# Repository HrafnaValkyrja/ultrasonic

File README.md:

# Stereo Ultrasound

A glasses-mounted wearable that shifts ultrasound (≈20–85 kHz) down into the audible range and plays it by bone conduction, in stereo, in real time.

- **Spec (source of truth):** [`docs/spec.md`](docs/spec.md). §1 is the owner-locked MVP.
- **Latest plan review:** [`docs/research/review-2026-09-30.md`](docs/research/review-2026-09-30.md)
- **Research findings:** [`docs/research/`](docs/research/), one file per task ID from spec §12.
- **Models and checks:** [`sim/checks/`](sim/checks/): PWM noise, noise-shaper comparison, dead-time distortion, weight balance. Run with `python3 <script>` (numpy, scipy).
- **Data:** [`sim/data/`](sim/data/): the mic's ultrasonic response, digitized from its datasheet.

Status: concept phase. Phase 1 (DSP simulation in Python) is next, pending owner decisions O1–O3 in spec §12.

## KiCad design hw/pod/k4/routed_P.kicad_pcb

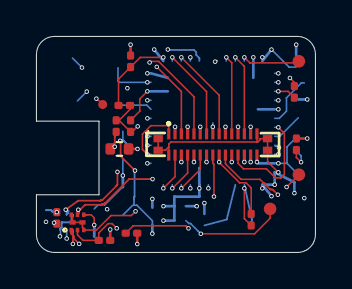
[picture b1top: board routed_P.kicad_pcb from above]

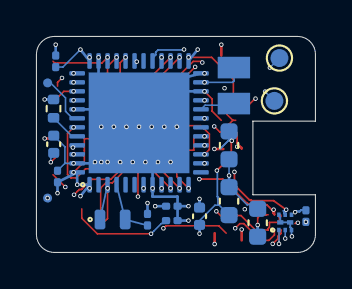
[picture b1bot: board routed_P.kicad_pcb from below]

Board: 6 copper layers, 15.5 x 12.0 mm, 37 parts (20 on the bottom side), 35 nets.

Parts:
C1, C2, C3, C6, C10: 100n; C_0201_0603Metric
C4, C7: 10u; C_0603_1608Metric
C5: 1u; C_0402_1005Metric
C8: 2u2 10V; C_0402_1005Metric
C9: 2u2 10V; C_0201_0603Metric
C11, C12: 8p2; C_0201_0603Metric
C14: 22u; C_0603_1608Metric
C22: 10n; C_0201_0603Metric
J1: XDCR_A; TestPoint_Pad_D1.0mm
J2: XDCR_B; TestPoint_Pad_D1.0mm
J21: BM28B0.6-30DP/2-0.35V(51); BM28B0.6-30DP_2-0.35V
L1: 2u2; L0806
Q1, Q2: PMCXB290UE; Nexperia_SOT1216_DFN1010B-6
R1: 10k; R_0402_1005Metric
R2: 33; R_0201_0603Metric
R3, R4, R5, R6: 100k; R_0201_0603Metric
R21: 0.1; R_0402_1005Metric
R22: 1k; R_0201_0603Metric
R23: 1M; R_0201_0603Metric
TP1: SWDIO; TestPoint_Pad_D0.7mm
TP2: SWCLK; TestPoint_Pad_D0.7mm
TP3: NRST; TestPoint_Pad_D0.7mm
TP7: DBG_TX; TestDot_D0.5mm
TP8: MDF_CCK; TestDot_D0.5mm
TP9: MDF_SDI; TestDot_D0.5mm
U1: STM32U575CIUxQ; QFN-48-1EP_7x7mm_P0.5mm_EP5.6x5.6mm
Y1: 32.768k 7pF; Crystal_SMD_2012-2Pin_2.0x1.2mm

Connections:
+3V0: C1.1, C2.1, C3.1, C4.1, C5.1, C6.1, C7.1, C14.1, J21.15, J21.30, J21.31, J21.32, J21.33, J21.34, Q1.4, Q2.4, R3.2, R5.2, R23.1, U1.1, U1.9, U1.21, U1.25, U1.36, U1.48
BRIDGE_RTN: Q1.1, Q2.1, R21.1, R22.1
BTN: J21.25, U1.10
CHG_INT: J21.23, U1.38
DBG_TX: TP7.1, U1.42
GA_N: Q1.2, R4.1, U1.17
GA_P: Q1.5, R3.1, U1.29
GB_N: Q2.2, R6.1, U1.28
GB_P: Q2.5, R5.1, U1.31
GND: C1.2, C2.2, C3.2, C4.2, C5.2, C6.2, C7.2, C8.2, C9.2, C10.2, C11.2, C12.2, C14.2, C22.2, J21.2, J21.4, J21.6, J21.8, J21.10, J21.12, J21.14, J21.16, J21.17, J21.18, J21.20, J21.22, J21.24, J21.26, J21.28, R1.2, R4.2, R6.2, R21.2, U1.8, U1.22, U1.24, U1.35, U1.41, U1.47, U1.49
I2C_SCL: J21.7, U1.26
I2C_SDA: J21.9, U1.27
I_SENSE: C22.1, R22.2, R23.2, U1.16
LED_K: J21.19, U1.43
LSE_IN: C11.1, U1.3, Y1.1
LSE_OUT: C12.1, U1.4, Y1.2
MDF_CCK: TP8.1, U1.45
MDF_SDI: TP9.1, U1.19
MIC_CLK: J21.3, R2.2
MIC_DATA: J21.21, U1.40
MIC_VDD: J21.1, U1.15
unnamed: R1.1, U1.44
unnamed: R2.1, U1.39
NRST: C10.1, TP3.1, U1.7
OUT_A: J1.1, Q1.3, Q1.6, Q1.7, Q1.8
OUT_B: J2.1, Q2.3, Q2.6, Q2.7, Q2.8
SWCLK: TP2.1, U1.37
SWDIO: TP1.1, U1.34
TS: J21.29, U1.12
USB_DM: J21.11, U1.32
USB_DP: J21.13, U1.33
VBAT_SENSE: J21.5, U1.14
VBUS_SENSE: J21.27, U1.11
VDD11: C8.1, C9.1, L1.2, U1.23, U1.46
VLXSMPS: L1.1, U1.20

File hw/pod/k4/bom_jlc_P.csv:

Comment,Designator,Footprint,LCSC Part #,Qty,In sourcing lock
100n,"C1,C10,C2,C3,C6",C_0201_0603Metric,C76934,5,yes
8p2,"C11,C12",C_0201_0603Metric,C161441,2,yes
22u,C14,C_0603_1608Metric,C59461,1,yes
10n,C22,C_0201_0603Metric,C85930,1,yes
10u,"C4,C7",C_0603_1608Metric,C19702,2,yes
1u,C5,C_0402_1005Metric,C52923,1,yes
2u2 10V,C8,C_0402_1005Metric,C107369,1,yes
2u2 10V,C9,C_0201_0603Metric,C318539,1,yes
BM28B0.6-30DP/2-0.35V(51),J21,BM28B0.6-30DP_2-0.35V,C424570,1,yes
2u2,L1,L0806,C337891,1,yes
PMCXB290UE,"Q1,Q2",Nexperia_SOT1216_DFN1010B-6,C19654206,2,yes
10k,R1,R_0402_1005Metric,C25744,1,yes
33,R2,R_0201_0603Metric,C473457,1,yes
0.1,R21,R_0402_1005Metric,C409058,1,yes
1k,R22,R_0201_0603Metric,C270365,1,yes
1M,R23,R_0201_0603Metric,C473482,1,yes
100k,"R3,R4,R5,R6",R_0201_0603Metric,C270364,4,yes
STM32U575CIUxQ,U1,QFN-48-1EP_7x7mm_P0.5mm_EP5.6x5.6mm,C5271013,1,yes
32.768k 7pF,Y1,Crystal_SMD_2012-2Pin_2.0x1.2mm,C99009,1,yes

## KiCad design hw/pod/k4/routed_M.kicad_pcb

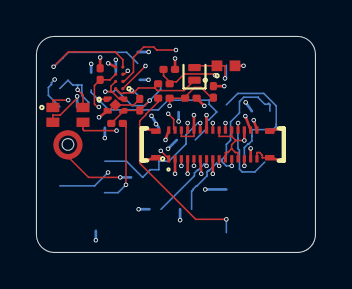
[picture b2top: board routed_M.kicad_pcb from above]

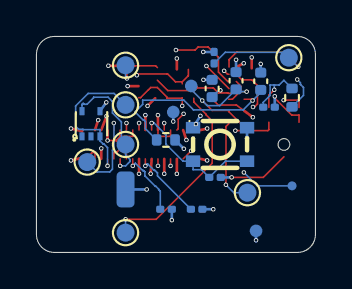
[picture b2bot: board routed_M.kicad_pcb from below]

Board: 6 copper layers, 15.5 x 12.0 mm, 38 parts (24 on the bottom side), 22 nets.

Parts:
C13, C19: 100n; C_0201_0603Metric
C15: 4u7 25V; C_0402_1005Metric
C16: 2u2 10V; C_0201_0603Metric
C17: 1u 16V; C_0201_0603Metric
C18: 1u; C_0402_1005Metric
C21: 10u; C_0402_1005Metric
D4: PMEG3005EL; D_SOD-882
D5: TPD1E10B06DPYR; X1SON-2_L1.0-W0.6-P0.65-BI-1
J3: VBUS; TestPoint_Pad_D1.0mm
J4: GND; WirePad_1.0x2.0mm
J5: BAT+; TestPoint_Pad_D1.0mm
J7: LED+; TestPoint_Pad_D1.0mm
J8: LED-; TestPoint_Pad_D1.0mm
J9: NTC; TestPoint_Pad_D1.0mm
J10: D+; TestPoint_Pad_D1.0mm
J11: D-; TestPoint_Pad_D1.0mm
J20: BM28B0.6-30DS/2-0.35V(51); BM28B0.6-30DS_2-0.35V
R8, R9: 1M; R_0201_0603Metric
R10, R14: 2k2; R_0201_0603Metric
R12, R13: 100k; R_0201_0603Metric
R15, R16: 10k; R_0201_0603Metric
R20: 0; R_0402_1005Metric
R30: 33; R_0402_1005Metric
RT1: 10k B3435; R_0201_0603Metric
SW1: KMT022NGJLHS; SW-SMD_4P-L3.0-W2.6-P1.85-LS3.4
TP4: 3V0; TestPoint_Pad_D0.7mm
TP5: GND; TestPoint_Pad_D0.7mm
TP6: VSYS; TestPoint_Pad_D0.7mm
TP10: MIC_DATA; TestDot_D0.5mm
U2: SPH0641LU4H-1; Knowles_LGA-5_3.5x2.65mm_Port0.65
U3: BQ25180YBGR; DSBGA-8_L1.6-W0.9-R2-C4-P0.40-BL
U4: TPS7A2030PDQNR; X2SON-4_L1.0-W1.0-P0.65-TL-EP
U6: TPD2E2U06DRLR; SOT-553-5_L1.6-W1.2-P0.50-LS1.6-TL-1

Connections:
+3V0: J20.15, J20.30, J20.31, J20.32, J20.33, J20.34, R15.2, R16.2, R20.2, SW1.1, SW1.2, TP4.1
BTN: J20.25, R10.1, SW1.3, SW1.4
CHG_INT: J20.23, U3.A1
DOCK_VBUS: D4.2, D5.1, J3.1
GND: C13.2, C15.2, C16.2, C17.2, C18.2, C19.2, C21.2, D5.2, J4.1, J20.2, J20.4, J20.6, J20.8, J20.10, J20.12, J20.14, J20.16, J20.17, J20.18, J20.20, J20.22, J20.24, J20.26, J20.28, R9.2, R10.2, R13.2, RT1.2, TP5.1, U2.2, U2.3, U3.D2, U4.2, U4.5, U6.4
I2C_SCL: J20.7, R15.1, U3.B1
I2C_SDA: J20.9, R16.1, U3.C1
LDO_OUT: C18.1, R20.1, U4.1
LED_A: J7.1, R14.2
LED_K: J8.1, J20.19
MIC_CLK: J20.3, U2.4
MIC_DATA: J20.21, TP10.1, U2.1
MIC_VDD: J20.1, R30.1
MIC_VDDF: C13.1, R30.2, U2.5
TS: J9.1, J20.29, RT1.1, U3.D1
USB_DM: J11.1, J20.11, U6.5
USB_DP: J10.1, J20.13, U6.3
VBAT: C16.1, J5.1, R8.1, U3.C2
VBAT_SENSE: C19.1, J20.5, R8.2, R9.1
VBUS: C15.1, D4.1, R12.1, U3.A2
VBUS_SENSE: J20.27, R12.2, R13.1
VSYS: C17.1, C21.1, R14.1, TP6.1, U3.B2, U4.3, U4.4

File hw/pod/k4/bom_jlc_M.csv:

Comment,Designator,Footprint,LCSC Part #,Qty,In sourcing lock
100n,"C13,C19",C_0201_0603Metric,C76934,2,yes
4u7 25V,C15,C_0402_1005Metric,C2858031,1,yes
2u2 10V,C16,C_0201_0603Metric,C318539,1,yes
1u 16V,C17,C_0201_0603Metric,C318540,1,yes
1u,C18,C_0402_1005Metric,C52923,1,yes
10u,C21,C_0402_1005Metric,C315248,1,yes
PMEG3005EL,D4,D_SOD-882,C282565,1,yes
TPD1E10B06DPYR,D5,X1SON-2_L1.0-W0.6-P0.65-BI-1,C48260,1,yes
BM28B0.6-30DS/2-0.35V(51),J20,BM28B0.6-30DP_2-0.35V,C424571,1,yes
2k2,"R10,R14",R_0201_0603Metric,C473508,2,yes
100k,"R12,R13",R_0201_0603Metric,C270364,2,yes
10k,"R15,R16",R_0201_0603Metric,C473048,2,yes
0,R20,R_0402_1005Metric,C17168,1,yes
33,R30,R_0402_1005Metric,C25105,1,yes
1M,"R8,R9",R_0201_0603Metric,C473482,2,yes
10k B3435,RT1,R_0201_0603Metric,C98098,1,yes
KMT022NGJLHS,SW1,SW-SMD_4P-L3.0-W2.6-P1.85-LS3.4,C221707,1,yes
SPH0641LU4H-1,U2,Knowles_LGA-5_3.5x2.65mm_Port0.65,C2879853,1,yes
BQ25180YBGR,U3,DSBGA-8_L1.6-W0.9-R2-C4-P0.40-BL,C3682423,1,yes
TPS7A2030PDQNR,U4,X2SON-4_L1.0-W1.0-P0.65-TL-EP,C5220164,1,yes
TPD2E2U06DRLR,U6,SOT-553-5_L1.6-W1.2-P0.50-LS1.6-TL-1,C1972959,1,yes

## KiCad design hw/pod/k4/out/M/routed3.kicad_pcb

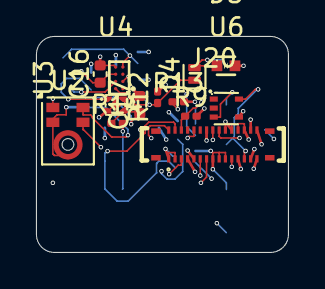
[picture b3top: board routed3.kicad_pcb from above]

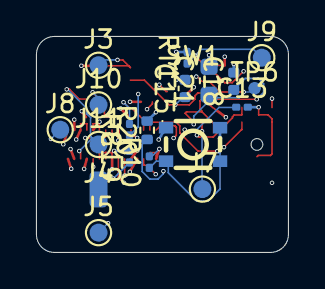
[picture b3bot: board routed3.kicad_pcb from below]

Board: 6 copper layers, 14.0 x 12.0 mm, 32 parts (19 on the bottom side), 21 nets.

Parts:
C13, C19: C_0201_0603Metric
C15, C16, C17, C18: C_0402_1005Metric
C21: C_0603_1608Metric
D4: D_SOD-882
D5: X1SON-2_L1.0-W0.6-P0.65-BI-1
J3, J5, J7, J8, J9, J10, J11: TestPoint_Pad_D1.0mm
J4: WirePad_1.0x2.0mm
J20: CONN-SMD_BM28B0.6-30DS-2-0.35V-51; BM28B0.6-30DS_2-0.35V
R8, R9, R10, R12, R13, R14: R_0201_0603Metric
R20: R_0402_1005Metric
RT1: R_0201_0603Metric
SW1: SW-SMD_4P-L3.0-W2.6-P1.85-LS3.4
TP6: TestPoint_Pad_D0.7mm
U2: Knowles_LGA-5_3.5x2.65mm; Knowles_LGA-5_3.5x2.65mm_Port0.65
U3: DSBGA-8_L1.6-W0.9-R2-C4-P0.40-BL
U4: X2SON-4_L1.0-W1.0-P0.65-TL-EP
U6: SOT-553-5_L1.6-W1.2-P0.50-LS1.6-TL-1

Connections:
+3V0: J20.17, J20.18, J20.19, R20.2, SW1.1, SW1.2
BTN: J20.29, R10.1, SW1.3, SW1.4
CHG_INT: J20.27, U3.A1
DOCK_VBUS: D4.2, D5.1, J3.1
GND: C13.2, C15.2, C16.2, C17.2, C18.2, C19.2, C21.2, D5.2, J4.1, J20.1, J20.2, J20.4, J20.5, J20.8, J20.9, J20.10, J20.12, J20.14, J20.15, J20.16, J20.20, J20.21, J20.24, R9.2, R10.2, R13.2, RT1.2, U2.2, U2.3, U3.D2, U4.2, U4.5, U6.4
I2C_SCL: J20.23, U3.B1
I2C_SDA: J20.25, U3.C1
LDO_OUT: C18.1, R20.1, U4.1
LED_A: J7.1, R14.2
LED_K: J8.1, J20.30
MIC_CLK: J20.3, U2.4
MIC_DATA: J20.7, U2.1
MIC_VDD: C13.1, J20.6, U2.5
TS: J9.1, J20.22, RT1.1, U3.D1
USB_DM: J11.1, J20.13, U6.5
USB_DP: J10.1, J20.11, U6.3
VBAT: C16.1, J5.1, R8.1, U3.C2
VBAT_SENSE: C19.1, J20.28, R8.2, R9.1
VBUS: C15.1, D4.1, R12.1, U3.A2
VBUS_SENSE: J20.26, R12.2, R13.1
VSYS: C17.1, C21.1, R14.1, TP6.1, U3.B2, U4.3, U4.4

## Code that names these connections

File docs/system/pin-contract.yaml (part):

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# Entry fields
#   id         function name (the net name where the net has one)
#   net        net name in the SKiDL schematic (hw/pod/gen.py), as in integration-map.md Section 3
#   via        for a net with no name of its own: {ref: R2, from_net: MIC_CLK} = the net on R2's OTHER terminal. The U1 pin is there
#   signal     required signal. An ST signal name (TIM1_CH1), or one of
#                GPIO        the pin is a plain GPIO; `modes` (Output, EXTI) must be in its IOModes
#                NRST        the reset pin (ST pin type Reset)
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  # ---- F1 hear: PDM clock out and data in on the ADF1 filter, supply switched by a GPIO
  - {id: MIC_CLK, via: {ref: R2, from_net: MIC_CLK}, signal: ADF1_CCK0, af: 3, role: "PDM clock to the mic through R2 33R (F1)"}
  - {id: MIC_DATA, net: MIC_DATA, signal: ADF1_SDI0, af: 3, role: "PDM data from the mic (F1)"}
  - {id: MIC_VDD, net: MIC_VDD, signal: GPIO, modes: [Output], role: "GPIO-switched mic supply, off in Off mode (F1, D12)"}
  # ---- F13 charger link
  - {id: I2C_SCL, net: I2C_SCL, signal: I2C2_SCL, af: 4, role: "charger I2C clock (F13)"}
  - {id: I2C_SDA, net: I2C_SDA, signal: I2C2_SDA, af: 4, role: "charger I2C data (F13)"}
  - {id: CHG_INT, net: CHG_INT, signal: GPIO, modes: [EXTI], role: "charger interrupt (F13): a GPIO with EXTI"}
  # ---- F10 USB data
  - {id: USB_DM, net: USB_DM, signal: USB_OTG_FS_DM, af: 10, role: "USB full-speed D- (F10)"}
  - {id: USB_DP, net: USB_DP, signal: USB_OTG_FS_DP, af: 10, role: "USB full-speed D+ (F10)"}
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  - {id: BOOT0, via: {ref: R1, from_net: GND}, signal: BOOT0, role: "BOOT0 held low by R1 10k (F14)"}
  # Rev F: BOOT_RX (R11 on PA10) and CC_SENSE (R19 on PA3) removed with their parts: the ROM loader pulls PA10 up itself
  # (AN2606 Rev 69 Table 199); charge-current policy comes from enumeration, not CC (simplification study PER-02, PWR-03)
  - {id: DBG_TX, net: DBG_TX, signal: USART1_TX, af: 7, role: "printf telemetry on TP7 (F14, O18; PER-12): SWO is lost to the mic clock on PB3"}
  - {id: MDF_CCK, net: MDF_CCK, signal: MDF1_CCK0, af: 5, role: "mic-clock fallback dot TP8 (F1, O18; sub-audio-in issue 5): hand-wire to R2's mic-side pad if the ADF clock duty fails"}
  - {id: MDF_SDI, net: MDF_SDI, signal: MDF1_SDI0, af: 6, role: "mic-data fallback dot TP9, wired to TP10 (MIC_DATA) in the fallback (F1, O18)"}
  # ---- F2 / F11 / F12
  - {id: LSE_IN, net: LSE_IN, signal: RCC_OSC32_IN, role: "32.768 kHz crystal (F2)"}
  - {id: LSE_OUT, net: LSE_OUT, signal: RCC_OSC32_OUT, role: "32.768 kHz crystal (F2)"}
  - {id: BTN, net: BTN, signal: PWR_WKUP1, role: "button wake from Off/Stop (F11)"}
  - {id: LED_K, net: LED_K, signal: TIM4_CH2, af: 2, role: "LED cathode, open-drain, duty set from VBAT (F12); gen.py: PB7 TIM4_CH2"}

# What the pins do besides their job. Sources are ST's datasheet and reference manual (text read 2026-10-02) and the audit
# docs/system/audit-datasheet-claims.md; ECR-0013 tracks every one.
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    cleared_by: {pin: PB5, net: GND}
  - port: PB15
    ecr: ECR-0013
    note: "UCPD dead battery: after reset a 5.1k pull-down (UCPD1_CC2) is activated by high level on PB14 (UCPD1_DBCC2 = I2C_SDA, idles high); a bridge N gate here is held OFF until PWR_UCPDR.UCPD_DBDIS is set"
    source: "ST DS13737 Rev 8 pin definitions table note 4; ECR-0013 S2"
    mitigation: firmware
  - port: PB4
    ecr: ECR-0013
    note: "after reset PB4 is NJTRST with an internal pull-up (30-50k to VDD): ~60 uA back-feeds the mic through MIC_DATA while its PA5-gated supply is off (reset, ROM DFU, Off); firmware must set PB4 analog / no pull before Off"
    source: "ST DS13737 Rev 8 pin definitions table note 5; RM0456 Rev 7 section 13.3.1 (audit claim 5)"
    mitigation: firmware
  - port: PA2
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  rule: "no switching node (VLXSMPS, VDD11, OUT_A/B) crosses the B2B; SMPS loop (U1, L1, C7, C8/C9) on one board (P)"
  on_M: "U2 mic + C13, U3 charger + C15/C16/C21, U4 LDO + C17/C18/R20, D4/D5/U6, dock pads J3/J4/J10/J11 (+2 magnets), SW1/R10, R8/R9/R12/R13/C19, RT1/J9, R14/J7/J8, J5, TP6, TP4/TP5/TP10, R15/R16 (I2C pull-ups), J20 (28 parts; rev 4 unload 2026-10-08)"
  on_P: "U1 + C1-C12, Y1, L1, R1/R2, Q1/Q2 + R3-R6, R21-R23/C22/C14, J1/J2, TP1-TP3/TP7-TP9, J21 (26 parts)"
  risks: ["BM28 numbering pin n <-> pin n and datasheet ratings [T]", "PA5/PB3/PB4 routing on P must stay away from L1/VLXSMPS (in-plane victim, V9 B_plus_noise.rerun_2026_10_08_partition_v2)"]

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
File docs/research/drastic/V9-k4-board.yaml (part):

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    noise: "same topology as today: port->L1 >= 12 mm, mic and MCU on one 17 mm board, 6L gives an extra inner-layer pair for mic return isolation. Unchanged risk class; tightest packing (MCU escape next to mic nets)."
  B_two_stacked_boards:
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    inter_board_signals: "~16-18 [E, pin-contract.yaml not read for the final map]: GND x4, VSYS x2 (bridge 315 mA peak, parallel pins), +3V0 x2, USB_DP, USB_DN, CHG_INT, I2C SDA/SCL (charger, PB6/PA1), BTN, plus 1-2 spares. 20-pin B2B suffices; 24 if SWD is routed through."
    L_mm: "~14.5 (range 14-15.5) [E]: floor from hard_floor (13.5) + 4 faces at ~U 0.35 + B2B footprint (~5.4 x 2 mm on each inner face) ; M is the length-setting board (QFN48 + L1 >= 12 mm behind the port); P can be shorter and ends earlier. Gain vs A(17): -2.5; vs A-WLCSP(15): only -0.5."
    pod_L_mm: "48.6"
    layers: "4L + 4L. Per-board ~100-118 pins on ~174 mm2 = 0.57-0.68 pins/mm2 = x1.05-1.25 of today's 0.543 (proven 4L ceiling x1.00, 'likely' <=1.15, 'possible' 1.15-1.5, V5 bands) -> 4L 'possible', 6L on M only is the fallback [M-L]"
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B_plus_noise:   # 2026-10-08 Claude (Opus 5.5 subagent). Sim: sim/noise/vertical_bplus.py (run_l2 reused unchanged, geometry hooks patched). Board: draft_r2 routed. H measured-by-model, all geometry/leak numbers [E] assumptions.
  rerun_2026_10_08_partition_v2:   # Claude (Opus 5.5 subagent), after the d2a70d9 review flaw (VLXSMPS/VDD11 crossed the B2B)
    partition: "ECR-0020 rev 2: P (upper) = U1 + SMPS (L1, C7, C8/C9) + charger + LDO + bridge + dock + button = ALL aggressors F01/F02; M (lower) = mic U2 + C13 only. B2B = BM28 10-pin: MIC_VDD, MIC_CLK, MIC_DATA + 7 GND. No switching node, no bridge or SMPS current crosses."
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  caveats:
    - "Margin to PSRR sign-off is thin in the pessimistic corner (4.8 dB < 10). Retire with a bring-up measurement (LN-V*) on a real stack; do not claim better than the model error (+-10 dB)."
    - "Conduction through BM28 not modelled (A6): the worst existing line (A01 conduction 15.3 dB) can only move down with extra series L/R in GND/VSYS. Needs >= 4 GND pins and a local 22 uF at the lower board (already in the B options)."
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    - "Mic is 1.08 mm, gap 0.6: the mic must be on the lower board's OUTER face; then the port opening is on the outer side and the planes shield the mic die from the upper board. If the mic sat inside the gap the shielding would drop out."
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  glossary: {PSRR: "power-supply rejection ratio of the mic", M_eff: "effective mutual inductance (nH) between aggressor and victim traces after plane screening", L1_body: "the 2.2 uH SMPS inductor modelled as one filament 0.5 mm off the board face"}
  noise:
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    why_not_extract_py: "extract.py/budget.py/pcbgeom.py assert 4 copper layers and ONE board; the MIC_VDD conduction network (U1 PA5 -> BM28 -> C13/mic) spans two boards and is not built. So conduction is NOT covered (K4-CONDUCT stays open)."
    result_margin_dB_F02_smps_on_mic_supply:   # tone chain, nominal / pessimistic PSRR / worst-case PSRR roll-off. sign-off needs >= 10 at worst
      today_draft_r2: [68.6, 48.6, 18.6]
      K4_traces_only_signed: [64.4, 44.4, 14.4]
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      - "owner decisions still open: ECR-0020/0021 approval, worst-PSRR noise corner, K4-BM28-DS contact R now read: signal <=100 mohm, power <=30 mohm max, K4-HEIGHTS, K4-STACK6."
    recommendation: "wait for K4-HEIGHTS + K4-STACK6 (both fast), then switch; making k4 default today would leave interfaces.py/bom_check/noise half-blind."
k4_mic_filter_2026_10_08:   # Claude (Opus 5.5 subagent). Follows k4_post_route_2026_10_08; ECR-0020 rev 5. P placement/routing not touched.
  glossary: {R30: "33 ohm series resistor on M between MIC_VDD (from P's PA5 via BM28 pin 6) and the mic-local net MIC_VDDF", MIC_VDDF: "filtered mic supply: U2 VDD + C13", K4-STACK6: "backlog item: record the JLC 6-layer 0.8 mm stack-up"}
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  model_corrections: "k4_noise.py c5899c1 did not mirror P (stack (x, 12 - y)) and put P file F.Cu on top; place_k4 says P file F is the INNER face. Fixed (--legacy-noflip reproduces the old geometry). Gap 0.6 (BM28 mated, [T]) instead of 1.3."
  result_F02_smps_to_mic_vdd_worst_PSRR_corner_dB:   # abs-bound margin with the L1 body, sign-off >= 10
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
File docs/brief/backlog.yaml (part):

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  - {id: ECR-0014/15/16, t: "simplification packages A/B/C still 'proposed'; superseded in practice by ECR-0018 (O25/O26)", opts: "close as superseded (rec) / keep open for the cherry-picks not in MZ-2", blk: owner}
  - {id: ECR-0018, t: "Phase-2 MZ-2 approved, implementation in progress, owner review in 1-2 weeks", blk: "owner (A-PHASE2-REVIEW)"}
  - {id: UI-5, t: "gesture model holes", opts: "A spec + timings / B short=mode, double=vol, hold=Off (rec) / C three holds", blk: owner, packet: "in packet 2 (coordinator, 2026-10-07)"}
  - {id: UI-8, dup: [PAD-13, ARM-8, 00-whole risk 3], t: "PB7 unprotected; pad-board LED_K 0.45 mm from OUT_B", opts: "A reorder pad-board pads / B R14 split / C both (rec)", blk: owner}
  - {id: PAD-1, dup: [PHYS-9], t: "contact face 50 mm2 vs O16(4) 100-150", opts: "A Sugru over whole cup face (rec) / B grow cup / C pre-made", blk: owner, packet: "in packet 2 (coordinator, 2026-10-07)"}
  - {id: PAD-3, t: "pad sealing", opts: "A dry test build, RTV final (rec) / B gasket / C pot", blk: owner}
  - {id: PAD-9, t: "pad board panel vs separate order", blk: "owner (JLC quote)"}
  - {id: SAI-4, t: "acoustic coupons vs O9", opts: "a JLC coupon panel / b rev-1 board + printed lids (rec) / c both", blk: owner}
  - {id: PROC-11, t: "SMPS inductor DFE201610E vs spec D5 LQM21PN", blk: "owner (spec or schematic)"}
  - {id: PROC-12, dup: [DBG-4], t: "O18 spare pins without pads (PA3 could sense VSYS)", blk: owner}
  - {id: PROC-2, dup: [ECR-0008], t: "MCU stock 8 at JLC; reserve vs U585 drop-in", blk: "owner (O21)"}
  - {id: PROC-3, t: "C7 CIN > 2 mm from pin 21", blk: "owner review O25"}
  - {id: DK-04, t: "sealed-pod update path", opts: "A write-protected boot stub + ROM DFU (rec) / B dual bank / C SWD-only", blk: owner}
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  - {id: DK-11, t: "dock magnets near L1: E11 whine on the right pod", k4: "magnets now D2.5 N52 at pod x 20.65/33.85 (zero-growth) beside L1 on P: E11 whine check"}
  - {id: SAI-5, t: "mic clock duty (scope R2.2)", k4: "mic clock PB3 crosses BM28 pin 3"}
  - {id: SAI-6, t: "RSFLT at 800 kHz swept tone", k4: "valid"}
  - {id: SAI-7, t: "MIC_VDD self-noise capture", k4: "MIC_VDD crosses BM28 pin 6"}
  - {id: SAI-11, t: "PB4 back-feed in reset/DFU: meter", k4: "valid"}
  - {id: SAI-13, t: "mic-port EQ notch constant refined from a bench sweep (r2 63.0 kHz Q6.4 -11.5 dB; K4 44.4 kHz Q6.8 -10.8 dB)", k4: "firmware variant-selectable 2026-10-08 (fw/variants.yaml mic_notch, folded into FW_DSP_EQ2, ULTRASONIC_DESIGN=k4); bench sweep refinement still open"}
  - {id: DBG-8, t: "ROM DFU pauses charging: check with a cell", k4: "valid"}
  - {id: RB-4, dup: [OUT-9 J-pad, 00-whole risk 1], t: "meter adjacent J pads in bring-up step 1", st: "stale-closed 2026-10-08 (K4: r2 J-pad adjacency meter step; K4 pad set differs (TP1-TP5 on P, dock pads on M) -> K4-BRINGUP)"}
  - {id: RPB-17, t: "600k-press + drop coupon (MZD-7) + 1.6 N kitchen-scale press test (UI-2 bench half)", note: "analysis done (UI-2)", k4: "SW1 on M belly; coupon + press test re-point to shell_k4"}
  - {id: UI-7, t: "LED VF at 0.1-1 mA", k4: "LED_K crosses BM28 pin 30"}
  - {id: ARM-1R, t: "heel exit dry fit with the real cell", k4: "heel reused in shell_k4"}
  - {id: ARM-2, t: "pad force dip on jaw opening; option pick after E12", opts: "A ~5 mm set (rec if k_t <= 5 N/mm) / B 0.85 wire / C deeper + saddle", k4: "valid"}
  - {id: ARM-3, t: "wire diameter: buy 0.8/0.85, pick on bench", k4: "valid"}
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  - {id: RPB-3, t: "body-side mic path", blk: "item:SAI-3, SAI-13", k4: "valid; SAI-3 unchanged; SAI-13 notch now 44.4 kHz (sim), sweep open"}

info_only:   # check WARNs that are tracked elsewhere, not work items
  - {id: CHK-PINS, t: "interfaces [pins] 3 known hazards (GB_N PB15, MIC_DATA PB4, TS PA2), ECR-0013 implemented"}
  - {id: CHK-SELFTEST, t: "interfaces [selftest] 5 skipped rules (design no longer has what they break)"}


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
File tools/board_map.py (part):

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    "CLOCK": ("Y1 32.768 kHz LSE + C11/C12", "RTC / LSE (PC14/PC15), C0G load caps", "#a4a9b0"),
    "MIC": ("U2 SPH0641LU4H-1 PDM mic", "ultrasonic mode; CLK PB3 via R2 33R, DATA PB4; VDD from PA5 (C13)", "#2fc98f"),
    "BRIDGE": ("H-bridge Q1/Q2 PMCXB290UE", "2x N+P pairs, 200 kHz AD PWM; R3-R6 100k gate pulls; C14 22 uF", "#f58a5c"),
    "SELFTEST": ("I_SENSE: R21 0.1R low-side shunt", "BRIDGE_RTN -> R22/C22 16 kHz LPF -> PA6 ADC1_IN11", "#ff6d6c"),
    "ARM_PADS": ("Arm pads J1/J2/J7/J8", "OUT_A/OUT_B to the exciter, LED_A/LED_K to the pad LED", "#f09bbd"),
    "DOCK_USB": ("Dock pads + protection", "D4 reverse-block Schottky; D5/D6 TPD1E10B06 (VBUS, CC); U6 TPD2E2U06 (D+/D-); R12/R13 VBUS_SENSE; R18 Rd 5k1", "#f2b632"),
    "CHARGER": ("U3 BQ25180 charger (DSBGA-8)", "I2C linear charger + power path: IN=VBUS, SYS=VSYS, BAT=VBAT; TS via RT1 or J9; R15/R16 I2C pull-ups", "#35b535"),
    "CELL_PADS": ("Cell pad J5", "", "#35b535"),
    "VBAT_SENSE": ("VBAT divider R8/R9 1M/1M + C19", "VBAT/2 -> PA4 (ADC4, runs in Stop 2)", "#7fd47f"),
    "LDO": ("U4 TPS7A2030 LDO", "VSYS -> 3.0 V (C17 in, C18 out); R20 0R link to +3V0", "#e8c86a"),
    "UI": ("SW1 KMT022 + LED drive", "SW1 -> PA0 WKUP1 (R10 2k2 pull-down); R14 2k2 LED series from VSYS, LED_K on PB7", "#e87ba4"),
    "DEBUG": ("Test pads", "TP1-6 SWDIO/SWCLK/NRST/3V0/GND/VSYS; TP7 USART1 TX printf; TP8-10 MDF mic fallback", "#c9ccd1"),
}
PAD_KEY_TECH = ("Wire pads:  5V = J3 DOCK_VBUS   G = J4 GND (dock + cell -)   B+ = J5 VBAT   T = J9 TS (cell NTC)   "
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
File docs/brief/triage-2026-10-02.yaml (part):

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    (reg-pod-body.md issue 11, L137), with a gap in the bottom ledge for the under-cell dock-wire route, plus a ''foam on support'' '
- id: Q35
  src: docs/system/reg-pad.md:121 (issue 13, 'Options (owner)')
  q: 'Protect PB7 from the pad-board LED_K/OUT_B adjacency and from arm-wire chafe: reorder the pads, split R14, or both?'
  verdict: claude-decides
  note: Option C, both. Reorder the pad-board pads to OUT_A, OUT_B, LED_A, LED_K (free; hw/padboard/layout.py L47-50). Split R14 into 1k + 1k, with one half in series with PB7. That caps fault current into
    PB7 at about 4.5 mA from VSYS or 3 mA from a bridge output, against its 20 mA absolute maximum. Today PB7 has no series re
- id: Q36
  src: docs/system/sub-dock-usb.md:107 (issue 4, 'pick one (owner)')
  q: 'Firmware update path for the sealed pod: a protected boot stub, dual-bank images, or SWD-only recovery?'
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

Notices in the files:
docs/system/pin-contract.yaml:
Verified against the open data on 2026-10-02 (pin-data commit and licence: tools/data/stm32_open_pin_data/SOURCE.md).
